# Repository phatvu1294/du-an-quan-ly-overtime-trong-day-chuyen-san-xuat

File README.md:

# Dự án quản lý overtime trong dây truyền sản xuất (public)
*Dự án quản lý overtime trong dây truyền sản xuất được phát triển trên LoRa, ESP32, Arduino và C# Winform*

### Giới thiệu
Đây là bản demo cho hệ thống quản lý overtime trong dây chuyền sản xuất để đánh giá hiệu quả công việc của từng line sản xuất.
Bản demo được thiết kế trên EAGLE với mạch một lớp, không tối ưu cho bảng mạch, để áp dụng trong thương mại vui lòng liên hệ tác giả.

### Mô tả hệ thống

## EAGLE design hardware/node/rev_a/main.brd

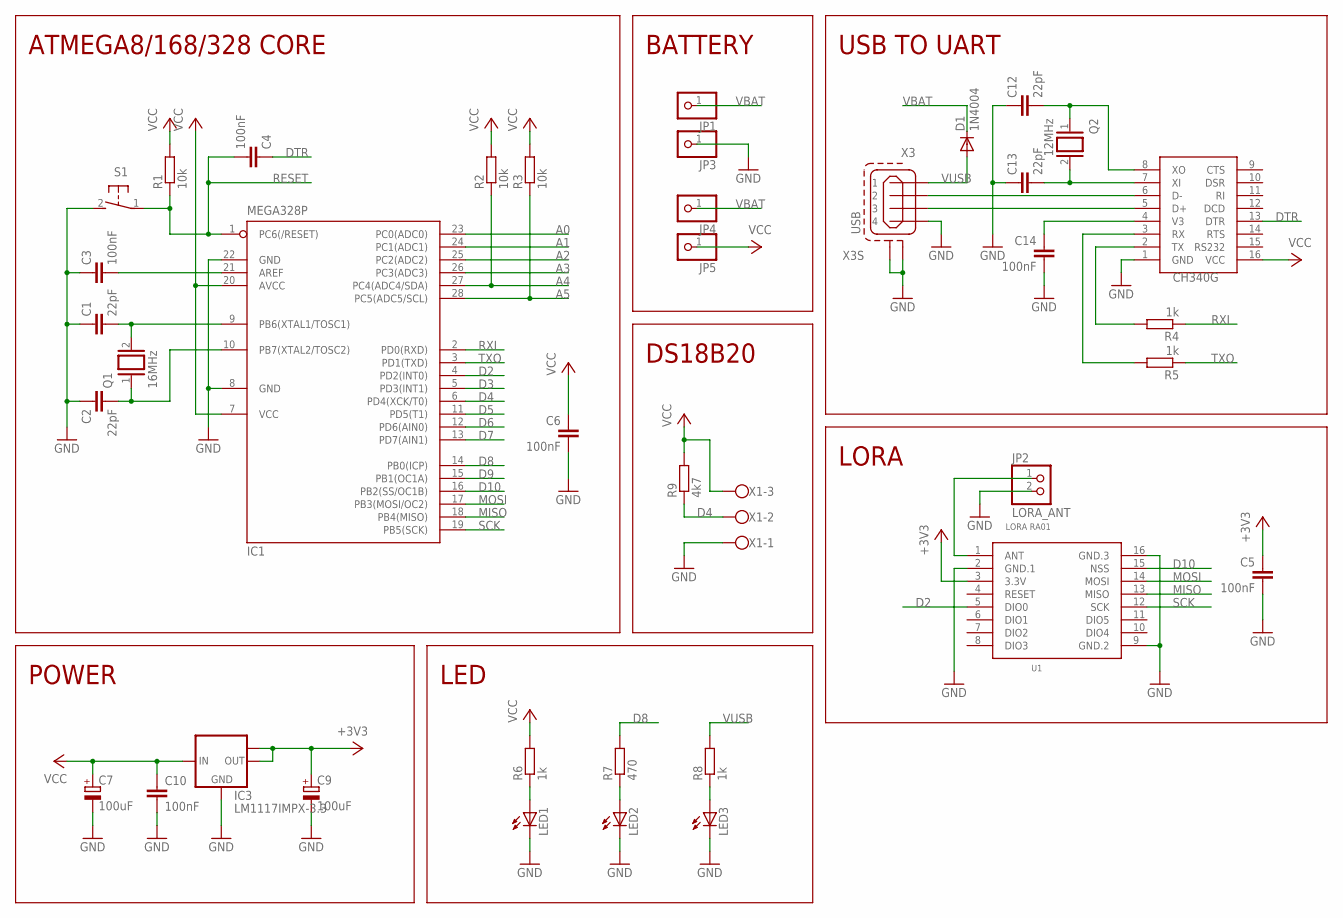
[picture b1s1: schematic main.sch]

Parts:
C1, C2, C12, C13: 22pF; C050-024X044
C3, C4, C5, C6, C10, C14: 100nF; C050-024X044
C7: 100uF; E3,5-10
C9: 100uF; E3,5-8
D1: 1N4004; DO41-10
IC1: MEGA328P; DIL28-3
IC3: LM1117IMPX-3.3; SOT223
JP1, JP3, JP4, JP5: PINHD-1X1; 1X01
JP2: LORA_ANT; 1X02
LED1, LED2, LED3: LED3MM
Q1: 16MHz; QS
Q2: 12MHz; QS
R1, R2, R3: 10k; 0207/10
R4, R5, R6, R8: 1k; 0207/10
R7: 470; 0207/10
R9: 4k7; 0207/10
S1: 31-XX; B3F-31XX
U1: LORA RA01; LORA-RA1-SMD
U$1: CH340G; SOIC16
X1: W237-103
X3: USB; 85-32004-00X

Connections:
+3V3: C5.1, C9.+, IC3.2 (OUT), IC3.TAB (OUT1), U1.3 (3.3V)
A0: IC1.23 (PC0(ADC0))
A1: IC1.24 (PC1(ADC1))
A2: IC1.25 (PC2(ADC2))
A3: IC1.26 (PC3(ADC3))
A4: IC1.27 (PC4(ADC4/SDA)), R2.1
A5: IC1.28 (PC5(ADC5/SCL)), R3.1
D2: IC1.4 (PD2(INT0)), U1.5 (DIO0)
D3: IC1.5 (PD3(INT1))
D4: IC1.6 (PD4(XCK/T0)), R9.1, X1.2
D5: IC1.11 (PD5(T1))
D6: IC1.12 (PD6(AIN0))
D7: IC1.13 (PD7(AIN1))
D8: IC1.14 (PB0(ICP)), R7.2
D9: IC1.15 (PB1(OC1A))
D10: IC1.16 (PB2(SS/OC1B)), U1.15 (NSS)
DTR: C4.1, U$1.13 (DTR)
GND: C1.1, C2.1, C3.1, C5.2, C6.2, C7.-, C9.-, C10.2, C12.1, C13.1, C14.2, IC1.8 (GND), IC1.22 (GND), IC3.1 (GND), JP2.2, JP3.1, LED1.K (C), LED2.K (C), LED3.K (C), S1.2 (S), U1.2 (GND.1), U1.9 (GND.2), U1.16 (GND.3), U$1.1 (GND), X1.1, X3.4, X3.M1 (S1), X3.M2 (S2)
MISO: IC1.18 (PB4(MISO)), U1.13 (MISO)
MOSI: IC1.17 (PB3(MOSI/OC2)), U1.14 (MOSI)
unnamed: JP2.1, U1.1 (ANT)
unnamed: LED3.A, R8.1
unnamed: U$1.6 (D-), X3.2
unnamed: C1.2, IC1.9 (PB6(XTAL1/TOSC1)), Q1.2
unnamed: C2.2, IC1.10 (PB7(XTAL2/TOSC2)), Q1.1
unnamed: C3.2, IC1.21 (AREF)
unnamed: LED1.A, R6.1
unnamed: LED2.A, R7.1
unnamed: U$1.5 (D+), X3.3
unnamed: C12.2, Q2.1, U$1.8 (XO)
unnamed: C13.2, Q2.2, U$1.7 (XI)
unnamed: C14.1, U$1.4 (V3)
unnamed: R5.2, U$1.3 (RX)
unnamed: R4.2, U$1.2 (TX)
RESET: C4.2, IC1.1 (PC6(/RESET)), R1.1, S1.1
RXI: IC1.2 (PD0(RXD)), R4.1
SCK: IC1.19 (PB5(SCK)), U1.12 (SCK)
TXO: IC1.3 (PD1(TXD)), R5.1
VBAT: D1.C, JP1.1, JP4.1
VCC: C6.1, C7.+, C10.1, IC1.7 (VCC), IC1.20 (AVCC), IC3.3 (IN), JP5.1, R1.2, R2.2, R3.2, R6.2, R9.2, U$1.16 (VCC), X1.3
VUSB: D1.A, R8.2, X3.1

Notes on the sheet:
LORA
ATMEGA8/168/328 CORE
USB TO UART
POWER
LED
BATTERY
DS18B20

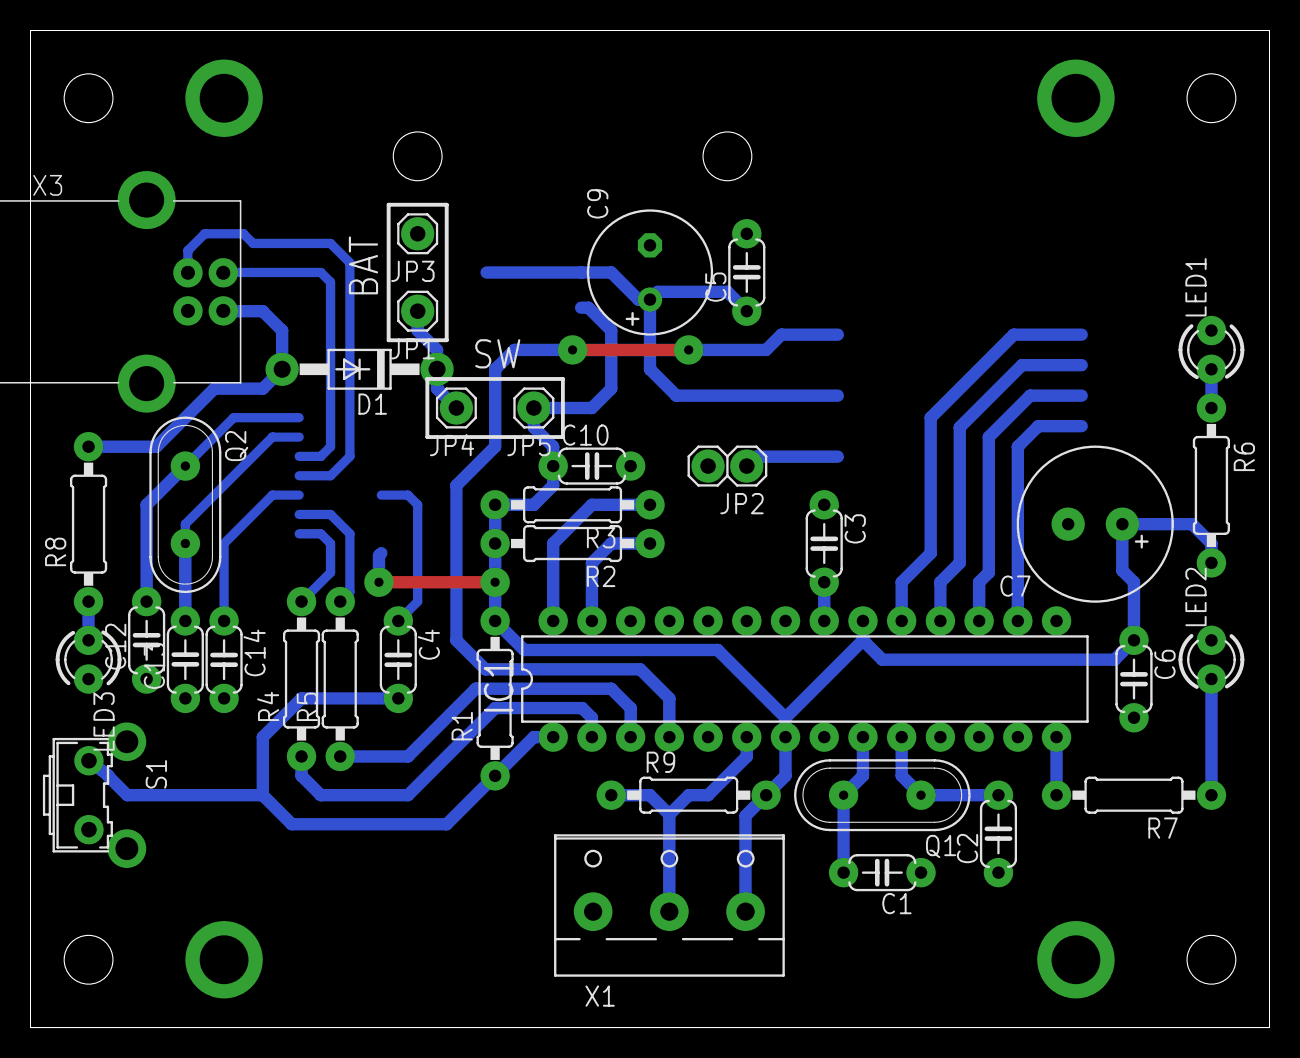
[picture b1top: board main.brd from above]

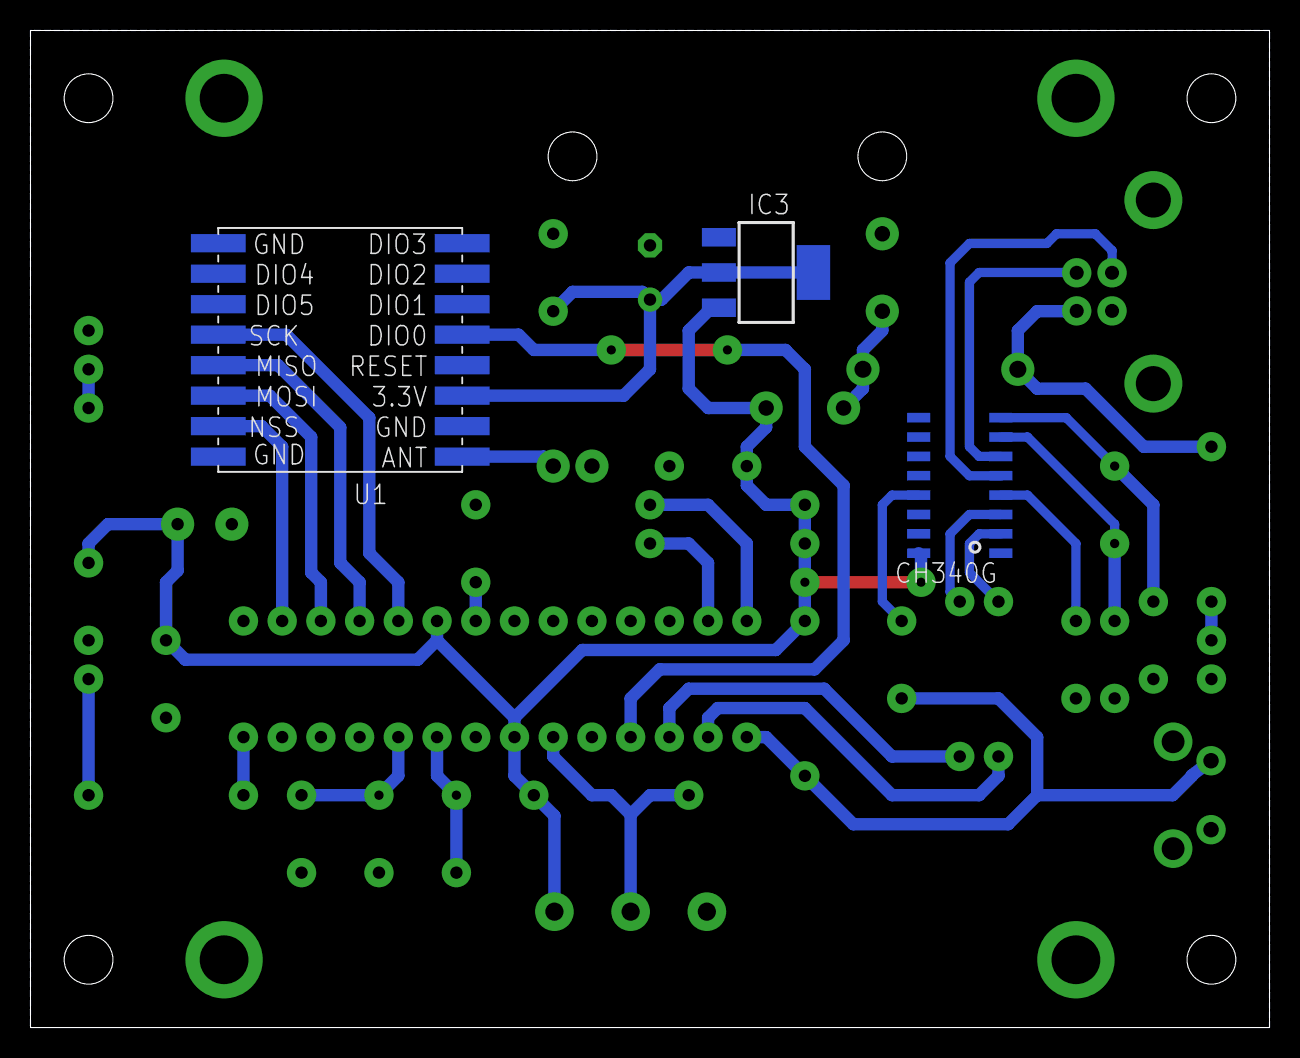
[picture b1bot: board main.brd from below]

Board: 2 copper layers, 81.3 x 65.4 mm, 39 parts (3 on the bottom side), 32 nets.

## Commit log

2021-04-05 upload source demo
2021-04-05 update source
2021-04-05 upload source image demo
